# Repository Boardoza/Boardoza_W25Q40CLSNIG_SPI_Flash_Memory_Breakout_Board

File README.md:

# Boardoza W25Q40CLSNIG Serial Flash Memory Breakout Board

The **Boardoza W25Q40CLSNIG** is a compact and high-performance **SPI Flash memory breakout board** built around the Winbond W25Q40CLSNIG chip. Offering **4 megabits (512 kilobytes)** of non-volatile storage, it is ideal for embedded applications requiring **code execution, configuration retention, or data logging**.

With support for **SPI communication up to 104 MHz**, this module enables fast and reliable read/write operations, even in timing-critical environments. The board is equipped with power and I/O indicators and is fully compatible with microcontrollers and single-board computers that require external SPI-based flash memory.

## [Click here to purchase!](https://www.ozdisan.com/maker-ve-iot-urunleri/boardoza/boardoza-modulleri/BOARDOZA-W25Q/1206520)

|Front Side|Back Side|
|:---:|:---:|
| | |

---

## Key Features

- **4M-bit / 512KB Serial Flash Memory:** Ideal for code or data storage in embedded systems.
- **Fast SPI Interface:** Operates at up to 104 MHz clock speed.
- **Flexible Erase Architecture:** Supports uniform 4KB sectors, and larger 32KB / 64KB block erase operations.
- **Durable & Reliable:** Over 100,000 write/erase cycles with >20 years of data retention.
- **Low Power Consumption:** Optimized for battery-powered systems.
- **Power LED Indicator (D1):** Helps monitor power state visually.

---

## Technical Specifications

**Model:** Winbond W25Q40CLSNIG  
**Input Voltage:** 3.3V – 5V  
**Functions:** Serial Flash Memory  
**Memory Size:** 4 Mbit (512KB)  
**Speed:** Up to 104 MHz  
**Interface:** SPI  
**Endurance:** 100,000+ write/erase cycles  
**Data Retention:** > 20 years  
**Operating Temperature:** -40°C ~ +85°C  
**Board Dimensions:** 20mm x 20mm  

---

## Board Pinout

### ( J1 ) Power and Basic SPI Interface

| Pin Number | Pin Name | Description |
|:---:|:---:|---|
| 1 | 5V   | Positive Power Supply |
| 2 | CLK  | Serial Clock Input (SCK) |
| 3 | DI   | Data Input (IO0 / MOSI) |
| 4 | GND  | Ground |

### ( J2 ) Additional SPI Control Pins

| Pin Number | Pin Name | Description |
|:---:|:---:|---|
| 1 | CS    | Chip Select (Active Low) |
| 2 | DO    | Data Output (IO1 / MISO) |
| 3 | WP    | Write Protect Input (IO2) |
| 4 | HOLD  | Hold Input (IO3) |

---

## Board Dimensions

---

## Step Files

[Boardoza W25Q40CLSNIG.step](./assets/W25Q40CLSNIG%20Step.step)

---

## Datasheet

[W25Q40CLSNIG Datasheet.pdf](./assets/W25Q40CLSNIG%20Datasheet.pdf)

---

## Version History

- V1.0.0 – Initial Release

---

## Support

For questions or technical support, please contact **<support@boardoza.com>**

---

## License

Shield: [![CC BY-SA 4.0][cc-by-sa-shield]][cc-by-sa]  

This work is licensed under a [Creative Commons Attribution-ShareAlike 4.0 International License][cc-by-sa].  

[![CC BY-SA 4.0][cc-by-sa-image]][cc-by-sa]  

[cc-by-sa]: http://creativecommons.org/licenses/by-sa/4.0/  
[cc-by-sa-image]: https://licensebuttons.net/l/by-sa/4.0/88x31.png  
[cc-by-sa-shield]: https://img.shields.io/badge/License-CC%20BY--SA%204.0-lightgrey.svg

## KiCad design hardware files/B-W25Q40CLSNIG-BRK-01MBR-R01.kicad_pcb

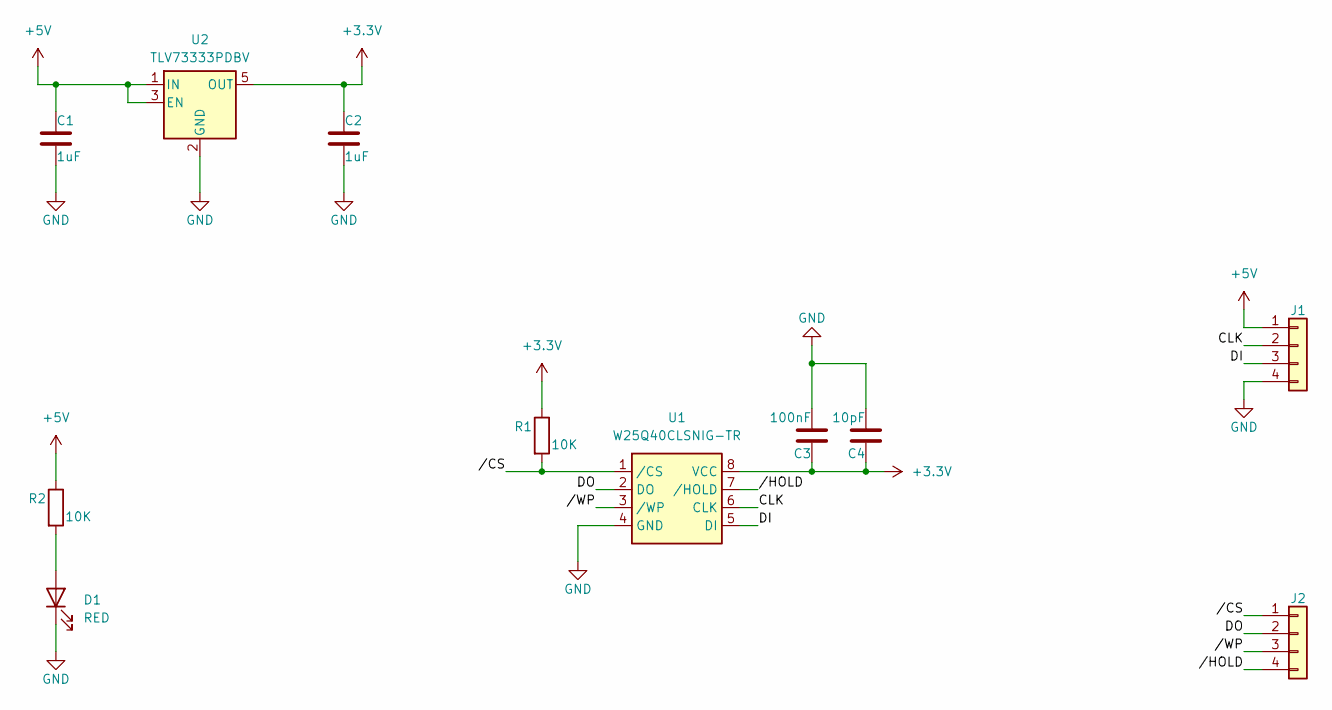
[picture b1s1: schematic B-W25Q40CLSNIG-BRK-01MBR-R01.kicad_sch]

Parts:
C1, C2: 1uF; C_0603_1608Metric
C3: 100nF; C_0603_1608Metric
C4: 10pF; C_0603_1608Metric
D1: RED; LED_0603_1608Metric
J1, J2: Conn_01x04; 2317-04S_1x04_P2.50mm_Vertical
R1, R2: 10K; R_0603_1608Metric
U1: W25Q40CLSNIG-TR; SOIC-8_3.9x4.9mm_P1.27mm
U2: TLV73333PDBV; SOT-23-5

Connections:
+3.3V: C2.1, C3.1, C4.1, R1.1, U1.8 (VCC), U2.5 (OUT)
+5V: C1.1, J1.1, R2.1, U2.1 (IN), U2.3 (EN)
/CLK: J1.2, U1.6 (CLK)
/DI: J1.3, U1.5 (DI)
/DO: J2.2, U1.2 (DO)
//CS: J2.1, R1.2, U1.1 (/CS)
//HOLD: J2.4, U1.7 (/HOLD)
//WP: J2.3, U1.3 (/WP)
GND: C1.2, C2.2, C3.2, C4.2, D1.1 (K), J1.4, U1.4 (GND), U2.2 (GND)
unnamed: D1.2 (A), R2.2

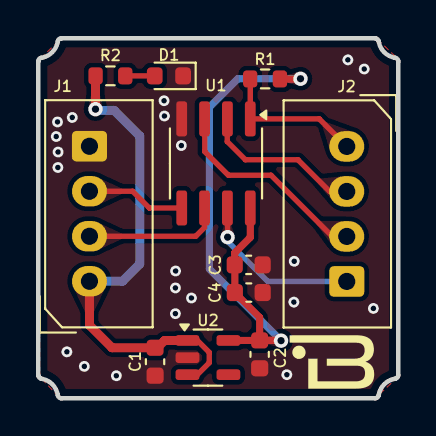
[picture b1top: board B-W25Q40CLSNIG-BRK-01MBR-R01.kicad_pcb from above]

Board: 2 copper layers, 20.0 x 20.0 mm, 11 parts (0 on the bottom side), 10 nets.

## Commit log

2025-04-04 Add W25Q40 library
